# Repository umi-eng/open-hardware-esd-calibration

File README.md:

# Open Hardware ESD Calibration

Open-source designs for calibrating and characterising ESD simulators.

## Safety

This repository contains hardware designs for calibrating and characterising ESD
simluators. These designs involve circuits that generate, measure, or are
exposed to high-votlage transients and are intended for use only be qualified
personel with appropriate training in eletrical safety and ESD/EMC test
practices.

These designs are provided "as is", with no warranty of any kind, express or
implied, including fitness for a particular purpose or safety in any given
application. See [LICENSE.txt](LICENSE.txt) (CERN-OHL-P-2.0) for full terms.

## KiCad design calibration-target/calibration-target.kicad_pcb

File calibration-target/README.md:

# ESD Calibration Target

This PCB conforms closely to the specification outlined in IEC 61000-4-2 Annex
B.

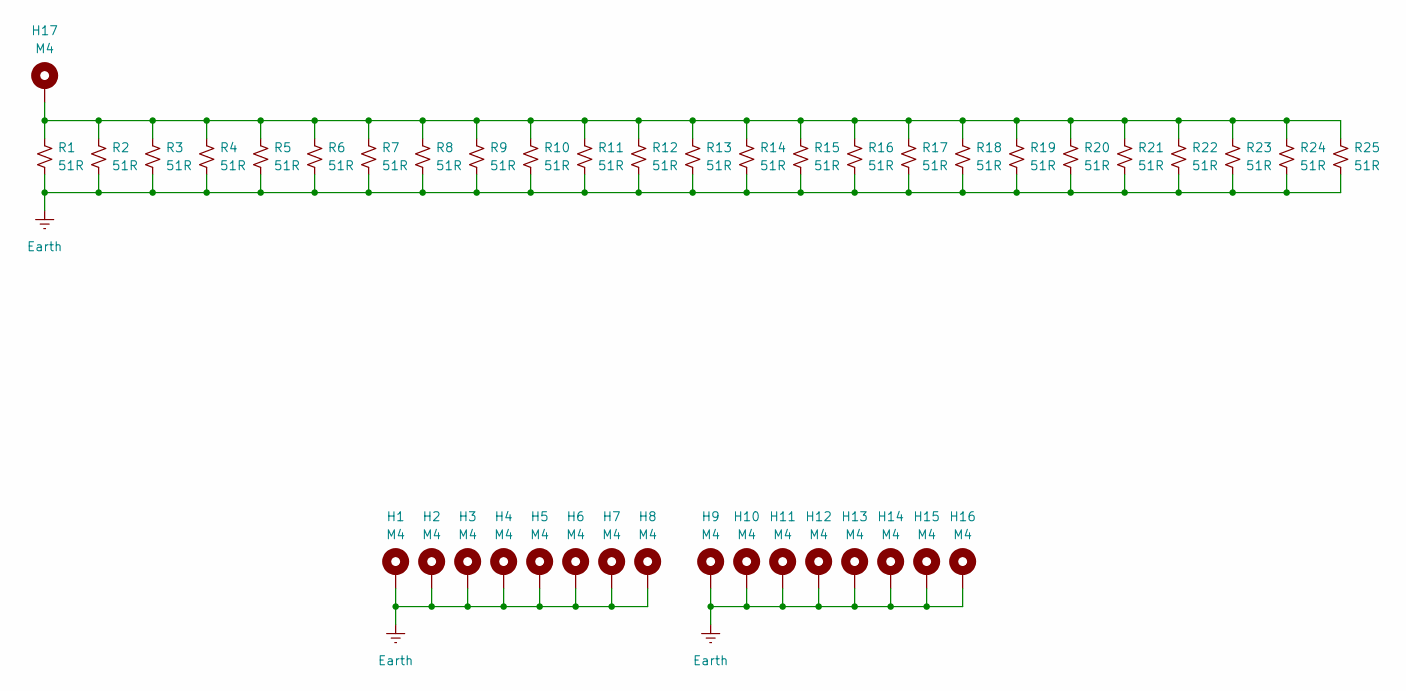
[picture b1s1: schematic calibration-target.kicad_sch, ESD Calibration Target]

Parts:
H1, H2, H3, H4, H5, H6, H7, H8: M4; MountingHole_4.3mm_M4_ISO14580_Pad
H9, H10, H11, H12, H13, H14, H15, H16, H17: M4; MountingHole_3.2mm_M3_ISO14580_Pad
R1, R2, R3, R4, R5, R6, R7, R8, R9, R10, R11, R12, R13, R14, R15, R16, R17, R18, R19, R20, R21, R22, R23, R24, R25: 51R; R_0603_1608Metric; Voltage 350V; Mouser 755-KTR03EZPF51R0

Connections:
Earth: H1.1 (1_1), H2.1 (1_1), H3.1 (1_1), H4.1 (1_1), H5.1 (1_1), H6.1 (1_1), H7.1 (1_1), H8.1 (1_1), H9.1 (1_1), H10.1 (1_1), H11.1 (1_1), H12.1 (1_1), H13.1 (1_1), H14.1 (1_1), H15.1 (1_1), H16.1 (1_1), R1.2, R2.2, R3.2, R4.2, R5.2, R6.2, R7.2, R8.2, R9.2, R10.2, R11.2, R12.2, R13.2, R14.2, R15.2, R16.2, R17.2, R18.2, R19.2, R20.2, R21.2, R22.2, R23.2, R24.2, R25.2
unnamed: H17.1 (1_1), R1.1, R2.1, R3.1, R4.1, R5.1, R6.1, R7.1, R8.1, R9.1, R10.1, R11.1, R12.1, R13.1, R14.1, R15.1, R16.1, R17.1, R18.1, R19.1, R20.1, R21.1, R22.1, R23.1, R24.1, R25.1

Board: 2 copper layers, 42 parts (0 on the bottom side), 2 nets, no tracks yet.

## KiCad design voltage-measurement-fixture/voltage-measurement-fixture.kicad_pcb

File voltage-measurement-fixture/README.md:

# ESD Voltage Measurement Fixture

A high impedance voltage divider for measuring the output voltage of an
ESD simulator.

A voltage divider built from 4x 50 MΩ resistors and 1x 1.1 MΩ resistor
reduces the input signal by a factor of 200 when read with a multimeter whose
internal resistance is ≈10 MΩ.

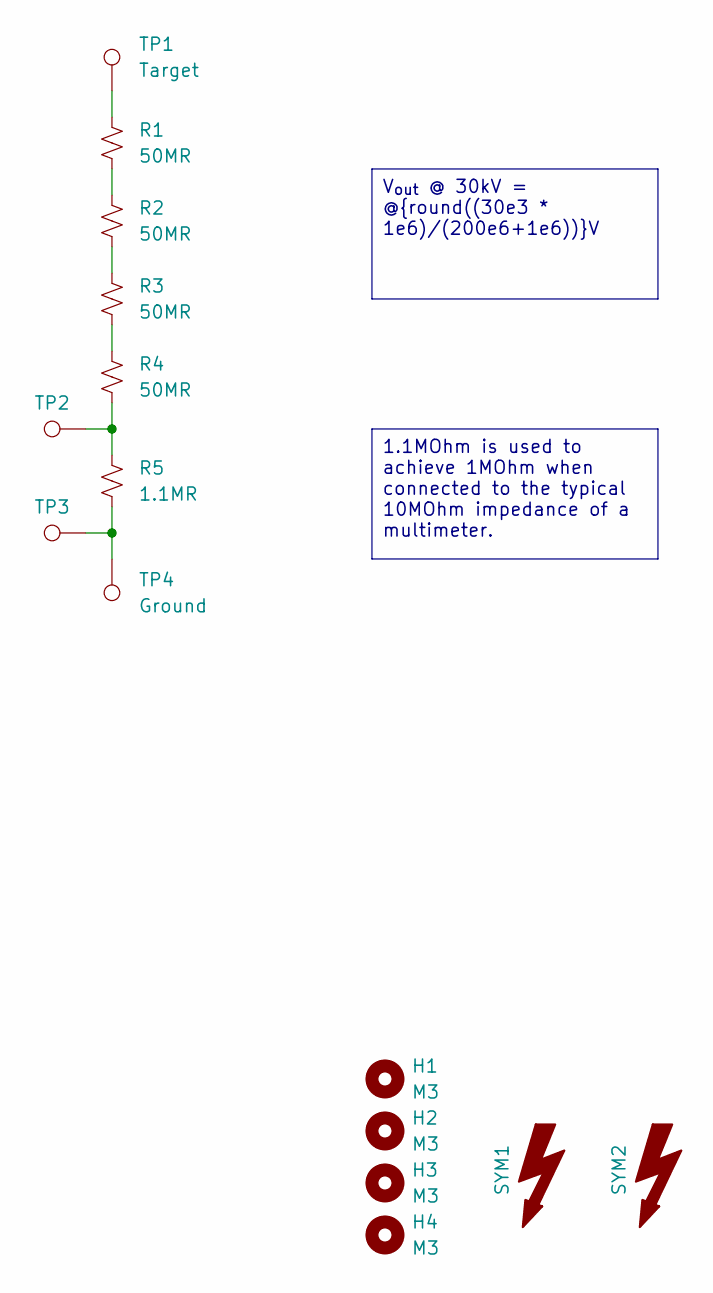
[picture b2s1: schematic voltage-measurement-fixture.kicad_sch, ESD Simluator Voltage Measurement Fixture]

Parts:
H1, H2, H3, H4: M3; MountingHole_3.2mm_M3_ISO14580
R1, R2, R3, R4: 50MR; R_Axial_DIN0414_L11.9mm_D4.5mm_P15.24mm_Horizontal; Voltage 8kV; Mouser 708-HVA12FA50M0
R5: 1.1MR; R_Axial_DIN0414_L11.9mm_D4.5mm_P15.24mm_Horizontal; Voltage 3.5kV; Mouser 594-HVR3700001104FR5
SYM1: SYM_Flash_Large; Symbol_HighVoltage_Triangle_8x7mm_Copper
SYM2: SYM_Flash_Large; Symbol_Attention_Triangle_8x7mm_Copper
TP1: Target; TestPoint_Pad_D4.0mm
TP2, TP3: TestPoint; TestPoint_Keystone_5005-5009_Compact
TP4: Ground; TestPoint_Pad_4.0x4.0mm

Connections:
unnamed: R1.1, TP1.1 (1_1)
unnamed: R1.2, R2.1
unnamed: R2.2, R3.1
unnamed: R3.2, R4.1
unnamed: R4.2, R5.1, TP2.1 (1_1)
unnamed: R5.2, TP3.1 (1_1), TP4.1 (1_1)

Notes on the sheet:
V_{out} @ 30kV = @{round((30e3 * 1e6)/(200e6+1e6))}V
1.1MOhm is used to achieve 1MOhm when connected to the typical 10MOhm impedance of a multimeter.

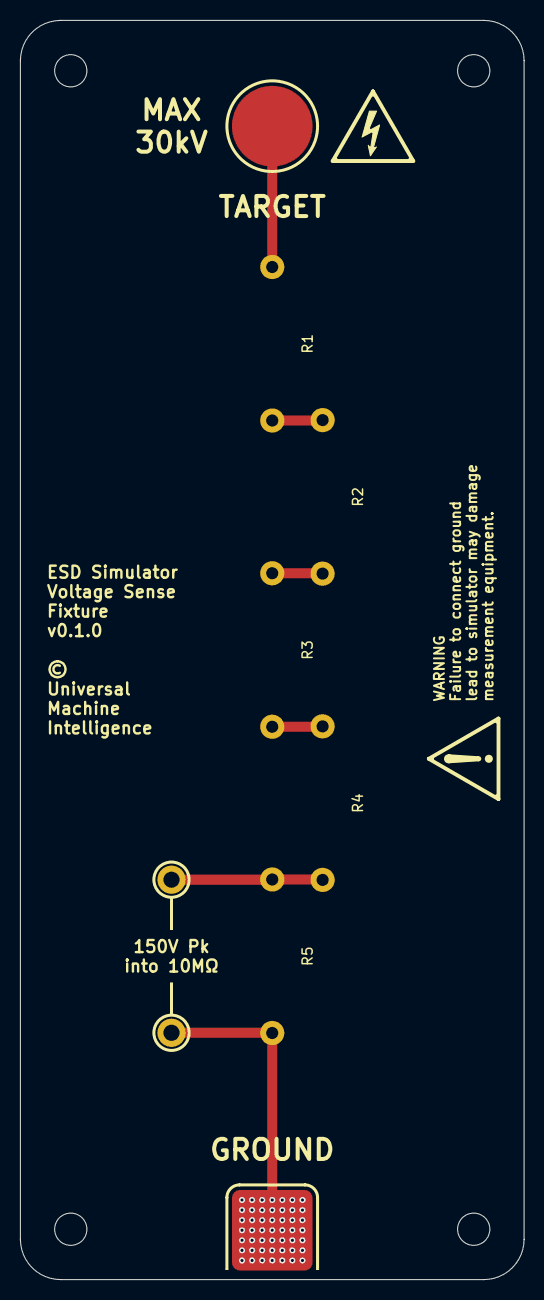
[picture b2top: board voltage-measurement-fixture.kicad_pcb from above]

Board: 2 copper layers, 50.0 x 125.0 mm, 15 parts (0 on the bottom side), 6 nets.

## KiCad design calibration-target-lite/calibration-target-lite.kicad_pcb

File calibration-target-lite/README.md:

# ESD Calibration Target Lite

This is a simplified low-cost calbration target consisting of only a PCB.

This will not perform as well as a proper IEC 61000-4-2 calibration target, but
it can still be useful for learning about ESD simulator waveforms and how to
probe them.

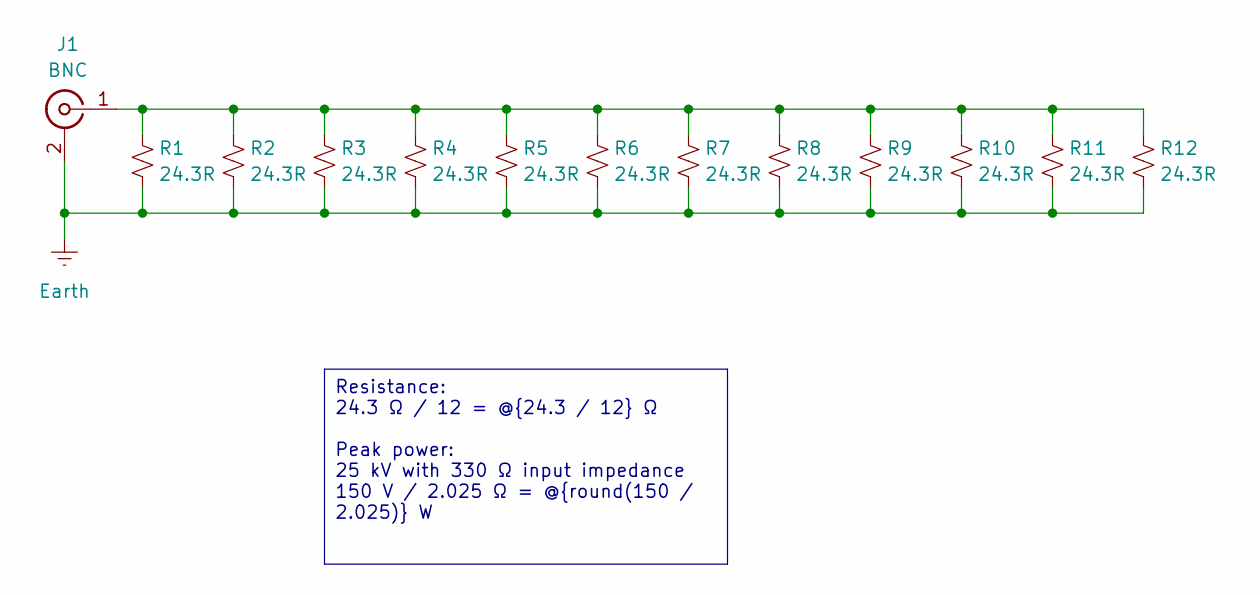
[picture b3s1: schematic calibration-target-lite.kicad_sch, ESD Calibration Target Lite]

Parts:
J1: BNC; BNC_TEConnectivity_1478035_Horizontal; Mouser 571-1-1337445-0
R1, R2, R3, R4, R5, R6, R7, R8, R9, R10, R11, R12: 24.3R; R_0603_1608Metric; Mouser 667-ERJ-PA3F24R3V

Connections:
Earth: J1.2 (Ext), R1.2, R2.2, R3.2, R4.2, R5.2, R6.2, R7.2, R8.2, R9.2, R10.2, R11.2, R12.2
unnamed: J1.1 (In), R1.1, R2.1, R3.1, R4.1, R5.1, R6.1, R7.1, R8.1, R9.1, R10.1, R11.1, R12.1

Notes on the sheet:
Resistance: 24.3 Ω / 12 = @{24.3 / 12} Ω Peak power: 25 kV with 330 Ω input impedance 150 V / 2.025 Ω = @{round(150 / 2.025)} W

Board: 2 copper layers, 13 parts (1 on the bottom side), 2 nets, no tracks yet.
